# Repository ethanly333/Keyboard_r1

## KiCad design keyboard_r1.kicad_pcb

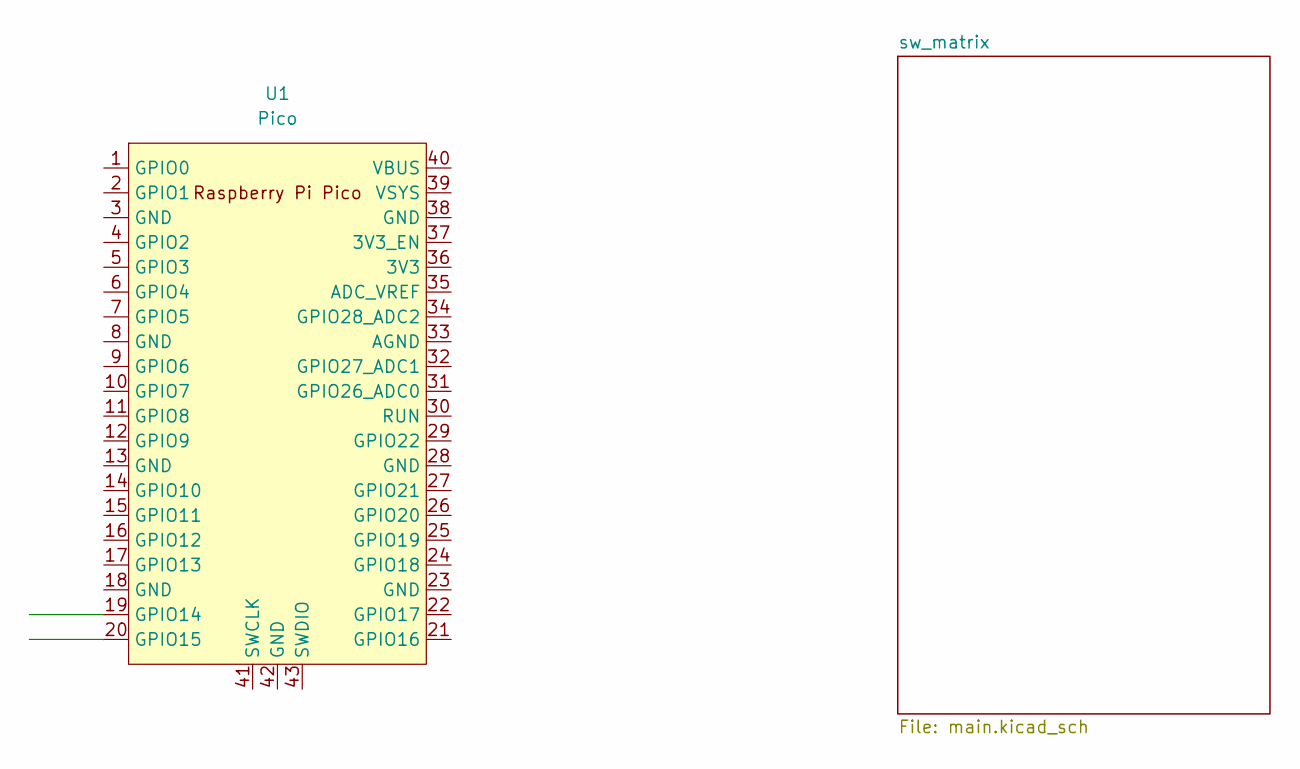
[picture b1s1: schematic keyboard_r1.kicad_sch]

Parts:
U1: Pico; RPi_Pico_SMD_TH

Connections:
ROW0: U1.20 (GPIO15); also elsewhere on the board
ROW1: U1.19 (GPIO14); also elsewhere on the board

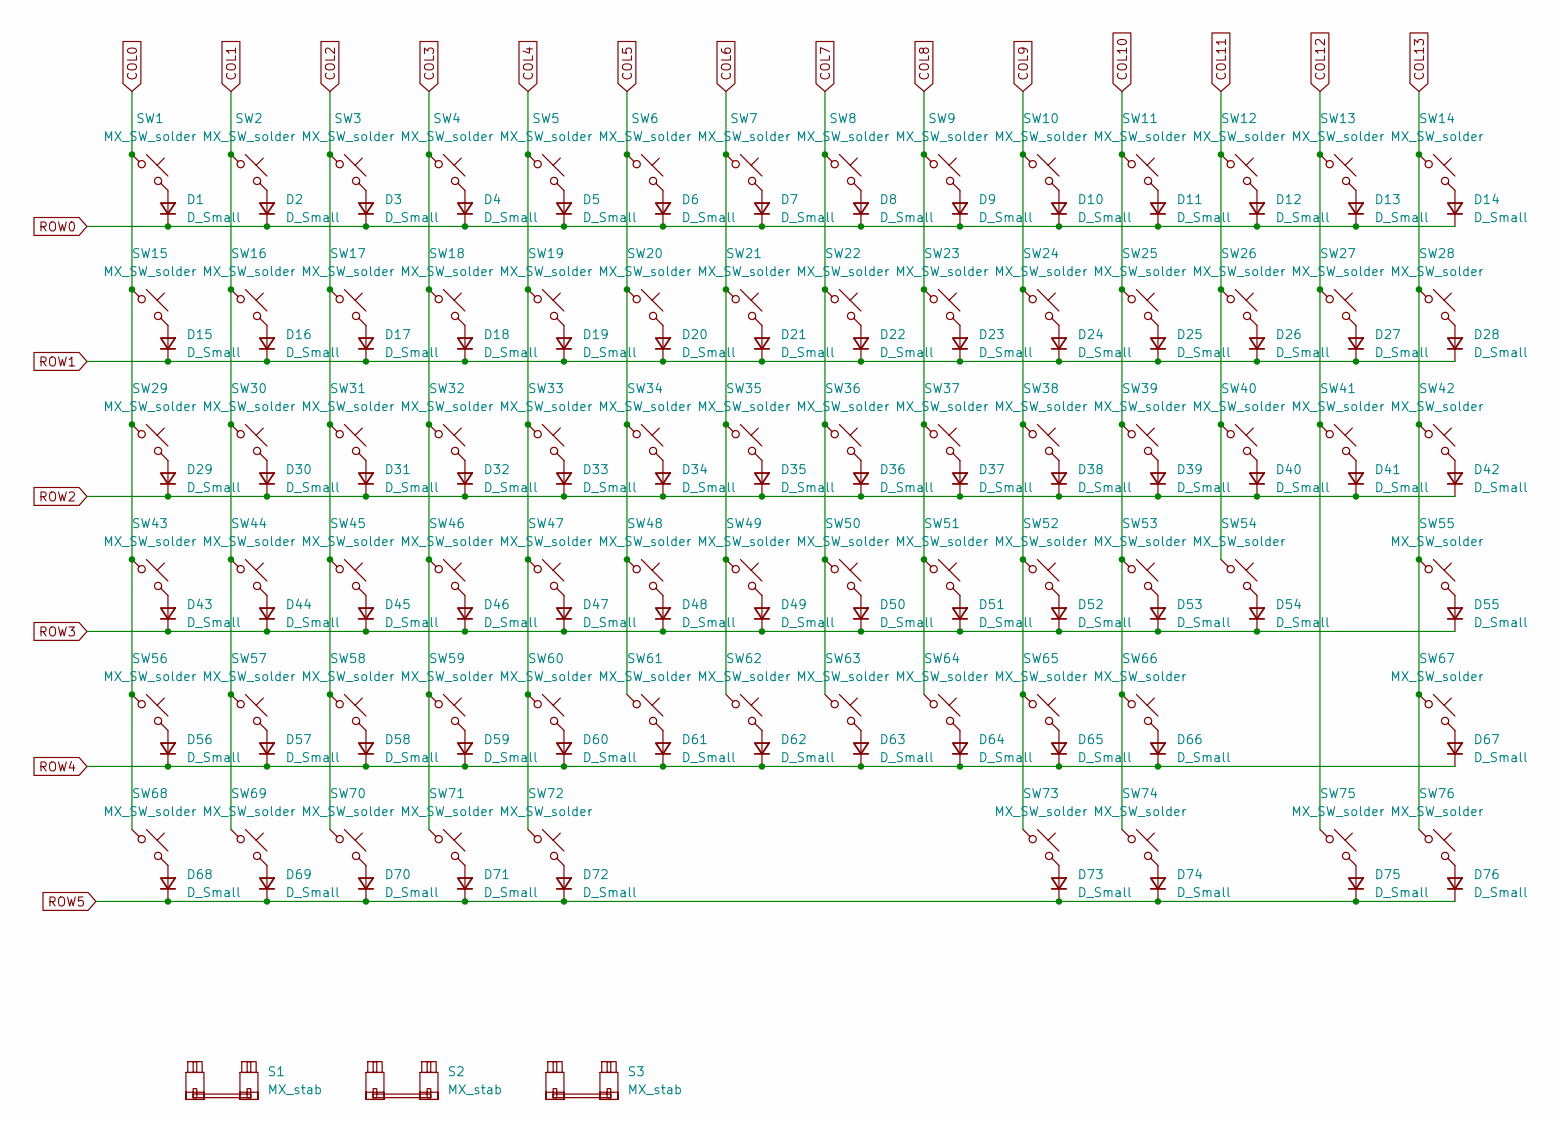
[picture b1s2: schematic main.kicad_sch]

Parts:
D1, D2, D3, D4, D5, D6, D7, D8, D9, D10, D11, D12, D13, D14, D15, D16, D17, D18, D19, D20, D21, D22, D23, D24, D25, D26, D27, D28, D29, D30, D31, D32, D33, D34, D35, D36, D37, D38, D39, D40, D41, D42, D43, D44, D45, D46, D47, D48, D49, D50, D51, D52, D53, D54, D55, D56, D57, D58, D59, D60, D61, D62, D63, D64, D65, D66, D67, D68, D69, D70, D71, D72, D73, D74, D75, D76: D_Small; D_SOD-123
S1: MX_stab; STAB_MX_P_6u
S2, S3: MX_stab; STAB_MX_P_2.25u
SW1, SW28, SW29: MX_SW_solder; SW_MX_1.5u
SW2, SW3, SW4, SW5, SW6, SW7, SW8, SW9, SW10, SW11, SW12, SW13, SW14, SW15, SW16, SW17, SW18, SW19, SW20, SW21, SW22, SW23, SW24, SW25, SW26, SW27, SW30, SW31, SW32, SW33, SW34, SW35, SW36, SW37, SW38, SW39, SW40, SW41, SW42, SW44, SW45, SW46, SW47, SW48, SW49, SW50, SW51, SW52, SW53, SW54, SW56, SW57, SW58, SW59, SW60, SW61, SW62, SW63, SW64, SW65, SW66, SW67, SW68, SW69, SW70, SW71, SW72, SW74, SW76: MX_SW_solder; SW_MX_1u
SW43, SW55: MX_SW_solder; SW_MX_1.75u
SW73, SW75: MX_SW_solder; SW_MX_1.25u

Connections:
COL0: SW1.1, SW15.1, SW29.1, SW43.1, SW56.1, SW68.1
COL1: SW2.1, SW16.1, SW30.1, SW44.1, SW57.1, SW69.1
COL2: SW3.1, SW17.1, SW31.1, SW45.1, SW58.1, SW70.1
COL3: SW4.1, SW18.1, SW32.1, SW46.1, SW59.1, SW71.1
COL4: SW5.1, SW19.1, SW33.1, SW47.1, SW60.1, SW72.1
COL5: SW6.1, SW20.1, SW34.1, SW48.1, SW61.1
COL6: SW7.1, SW21.1, SW35.1, SW49.1, SW62.1
COL7: SW8.1, SW22.1, SW36.1, SW50.1, SW63.1
COL8: SW9.1, SW23.1, SW37.1, SW51.1, SW64.1
COL9: SW10.1, SW24.1, SW38.1, SW52.1, SW65.1, SW73.1
COL10: SW11.1, SW25.1, SW39.1, SW53.1, SW66.1, SW74.1
COL11: SW12.1, SW26.1, SW40.1, SW54.1
COL12: SW13.1, SW27.1, SW41.1, SW75.1
COL13: SW14.1, SW28.1, SW42.1, SW55.1, SW67.1, SW76.1
unnamed: D1.2 (A), SW1.2
unnamed: D2.2 (A), SW2.2
unnamed: D3.2 (A), SW3.2
unnamed: D4.2 (A), SW4.2
unnamed: D5.2 (A), SW5.2
unnamed: D6.2 (A), SW6.2
unnamed: D7.2 (A), SW7.2
unnamed: D8.2 (A), SW8.2
unnamed: D9.2 (A), SW9.2
unnamed: D10.2 (A), SW10.2
unnamed: D11.2 (A), SW11.2
unnamed: D12.2 (A), SW12.2
unnamed: D13.2 (A), SW13.2
unnamed: D14.2 (A), SW14.2
unnamed: D15.2 (A), SW15.2
unnamed: D16.2 (A), SW16.2
unnamed: D17.2 (A), SW17.2
unnamed: D18.2 (A), SW18.2
unnamed: D19.2 (A), SW19.2
unnamed: D20.2 (A), SW20.2
unnamed: D21.2 (A), SW21.2
unnamed: D22.2 (A), SW22.2
unnamed: D23.2 (A), SW23.2
unnamed: D24.2 (A), SW24.2
unnamed: D25.2 (A), SW25.2
unnamed: D26.2 (A), SW26.2
unnamed: D27.2 (A), SW27.2
unnamed: D28.2 (A), SW28.2
unnamed: D29.2 (A), SW29.2
unnamed: D30.2 (A), SW30.2
unnamed: D31.2 (A), SW31.2
unnamed: D32.2 (A), SW32.2
unnamed: D33.2 (A), SW33.2
unnamed: D34.2 (A), SW34.2
unnamed: D35.2 (A), SW35.2
unnamed: D36.2 (A), SW36.2
unnamed: D37.2 (A), SW37.2
unnamed: D38.2 (A), SW38.2
unnamed: D39.2 (A), SW39.2
unnamed: D40.2 (A), SW40.2
unnamed: D41.2 (A), SW41.2
unnamed: D42.2 (A), SW42.2
unnamed: D43.2 (A), SW43.2
unnamed: D44.2 (A), SW44.2
unnamed: D45.2 (A), SW45.2
unnamed: D46.2 (A), SW46.2
unnamed: D47.2 (A), SW47.2
unnamed: D48.2 (A), SW48.2
unnamed: D49.2 (A), SW49.2
unnamed: D50.2 (A), SW50.2
unnamed: D51.2 (A), SW51.2
unnamed: D52.2 (A), SW52.2
unnamed: D53.2 (A), SW53.2
unnamed: D54.2 (A), SW54.2
unnamed: D55.2 (A), SW55.2
unnamed: D56.2 (A), SW56.2
unnamed: D57.2 (A), SW57.2
unnamed: D58.2 (A), SW58.2
unnamed: D59.2 (A), SW59.2
unnamed: D60.2 (A), SW60.2
unnamed: D61.2 (A), SW61.2
unnamed: D62.2 (A), SW62.2
unnamed: D63.2 (A), SW63.2
unnamed: D64.2 (A), SW64.2
unnamed: D65.2 (A), SW65.2
unnamed: D66.2 (A), SW66.2
unnamed: D67.2 (A), SW67.2
unnamed: D68.2 (A), SW68.2
unnamed: D69.2 (A), SW69.2
unnamed: D70.2 (A), SW70.2
unnamed: D71.2 (A), SW71.2
unnamed: D72.2 (A), SW72.2
unnamed: D73.2 (A), SW73.2
unnamed: D74.2 (A), SW74.2
unnamed: D75.2 (A), SW75.2
unnamed: D76.2 (A), SW76.2
ROW0: D1.1 (K), D2.1 (K), D3.1 (K), D4.1 (K), D5.1 (K), D6.1 (K), D7.1 (K), D8.1 (K), D9.1 (K), D10.1 (K), D11.1 (K), D12.1 (K), D13.1 (K), D14.1 (K); also elsewhere on the board
ROW1: D15.1 (K), D16.1 (K), D17.1 (K), D18.1 (K), D19.1 (K), D20.1 (K), D21.1 (K), D22.1 (K), D23.1 (K), D24.1 (K), D25.1 (K), D26.1 (K), D27.1 (K), D28.1 (K); also elsewhere on the board
ROW3: D56.1 (K), D57.1 (K), D58.1 (K), D59.1 (K), D60.1 (K), D61.1 (K), D62.1 (K), D63.1 (K), D64.1 (K), D65.1 (K), D66.1 (K), D67.1 (K)
ROW4: D68.1 (K), D69.1 (K), D70.1 (K), D71.1 (K), D72.1 (K), D73.1 (K), D74.1 (K), D75.1 (K), D76.1 (K)

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
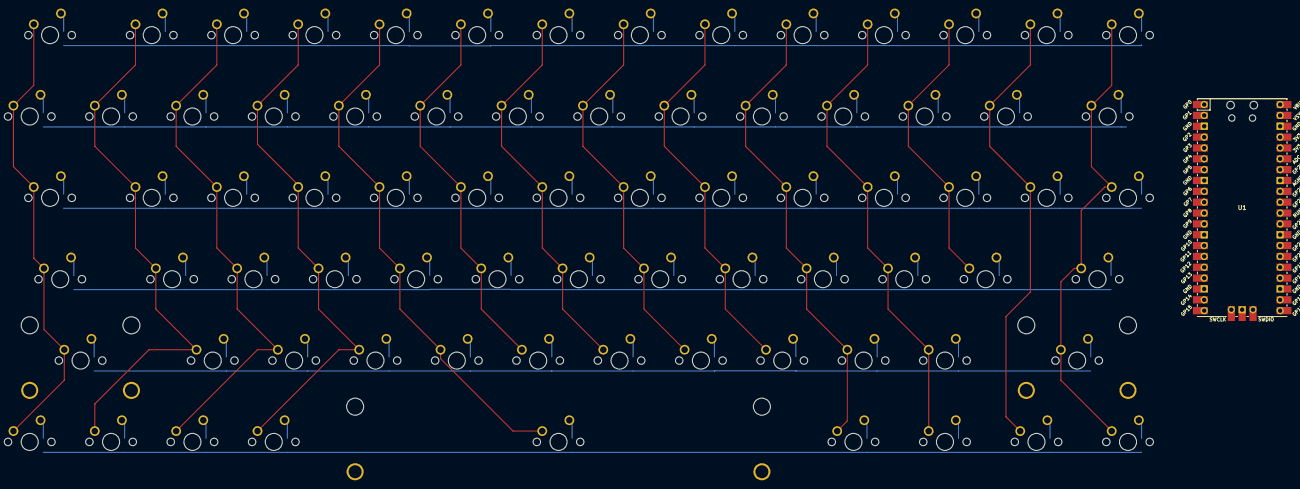
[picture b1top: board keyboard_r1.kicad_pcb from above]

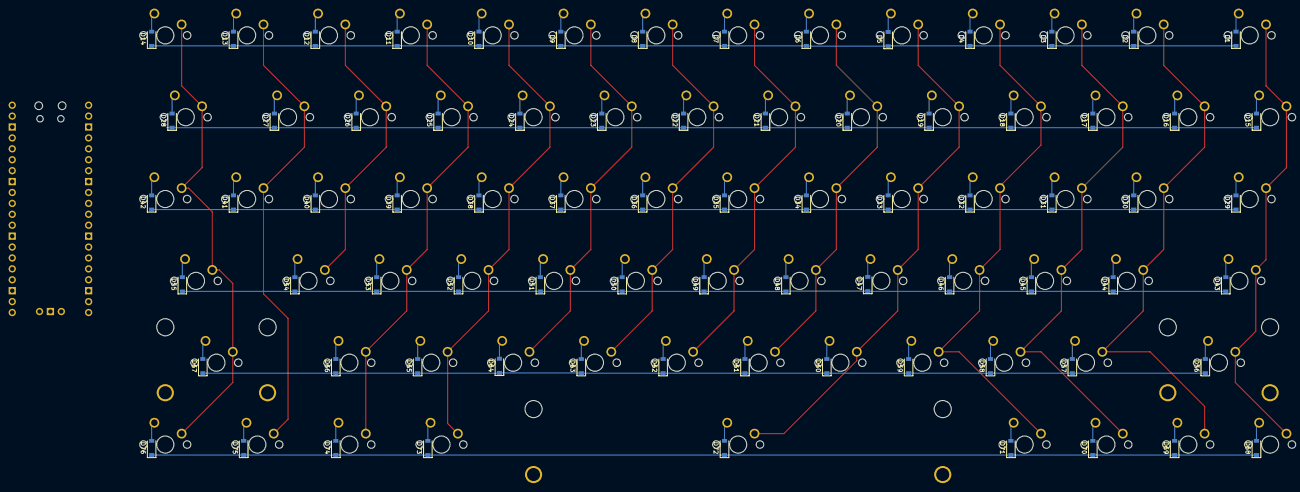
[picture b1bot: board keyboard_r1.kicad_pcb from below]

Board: 2 copper layers, 156 parts (76 on the bottom side), 95 nets.

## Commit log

2024-02-08 init kicad 6.0 proj
2024-02-08 init marbastlib
2024-02-08 sw matrix schematic completed
2024-02-09 sw matrix layout is complete
2024-02-09 sw matrix traces are laid
2024-02-12 added Raspberry Pi Pico componenet
2024-02-19 added all global labels
